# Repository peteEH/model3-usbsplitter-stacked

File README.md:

# model3-usbsplitter-stacked
stacked usb splitter for model 3, end launch

BOM to get the splitter assembled

Part Number     Quantity    Comments
5787745-2       1           double stacked, type-A, USB receptacle
UP2-AH-1-TH     1           plug, type-A, usb
4.7uF Cap       1           Any capacitor, 0805 package, 10V or higher rating, 1uF to 6.8uF cap range
2 ohm res       1           0805 package, 1.5 to 3 ohms
22uF Cap        1           Any capacitor, 1210 package, 10V or higher rating, 10uF to 47uF cap range

PCB             1           Order PCB from JLC PCB or similar fab house   (QTY 5 for $2 @ JLC)

## LICENSE ##
Hardware License is Creative Commons - Attribution 3.0

Feel free to use these files to learn, explore electronics.

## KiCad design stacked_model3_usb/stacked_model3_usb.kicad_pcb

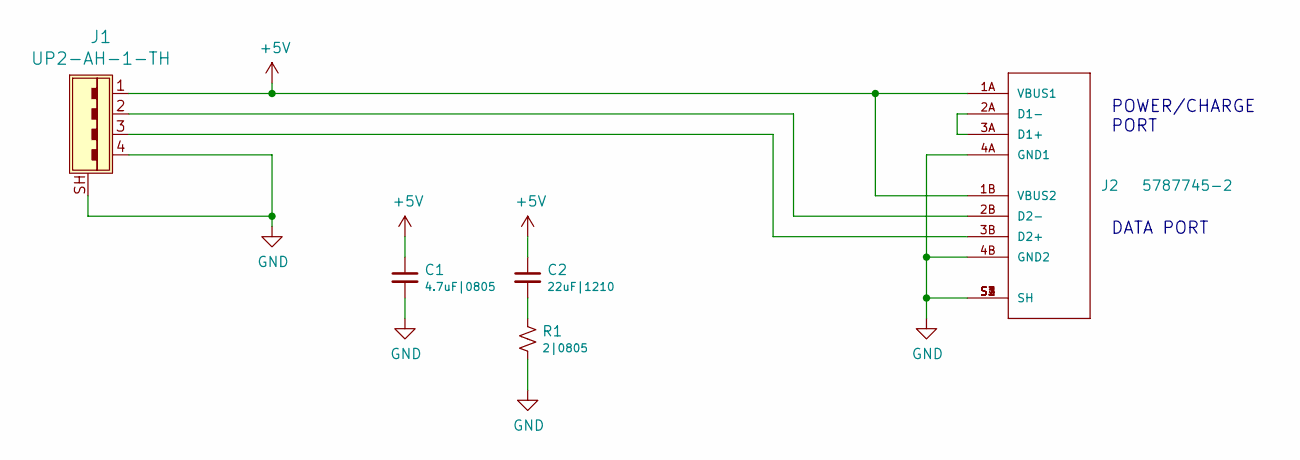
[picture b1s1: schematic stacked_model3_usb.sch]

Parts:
C1: 4.7uF|0805; C_0805_2012Metric
C2: 22uF|1210; C_1210_3225Metric
J1: UP2-AH-1-TH; USB_Male_A_UP2-AH-1-TH; MPN UP2-AH-1-TH; Digi-Key_PN 102-3996-ND
J2: 5787745-2; TE_5787745-2
R1: 2|0805; R_0805_2012Metric

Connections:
+5V: C1.1, C2.1, J1.1, J2.1A (VBUS1), J2.1B (VBUS2)
GND: C1.2, J1.4, J1.SH, J2.4A (GND1), J2.4B (GND2), J2.S1 (SH), J2.S2 (SH), J2.S3 (SH), J2.S4 (SH), R1.2
unnamed: C2.2, R1.1
unnamed: J1.2, J2.2B (D2-)
unnamed: J1.3, J2.3B (D2+)
unnamed: J2.2A (D1-), J2.3A (D1+)

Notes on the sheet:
DATA PORT
POWER/CHARGE PORT

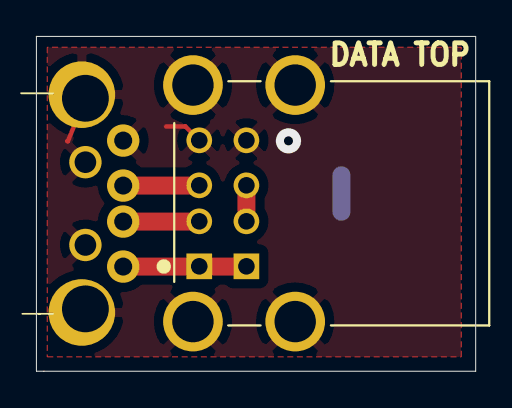
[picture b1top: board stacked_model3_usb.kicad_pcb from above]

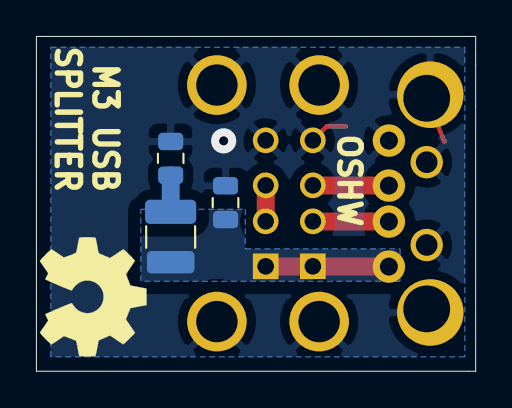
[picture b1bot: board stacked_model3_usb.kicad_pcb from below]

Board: 2 copper layers, 24.4 x 18.6 mm, 5 parts (3 on the bottom side), 6 nets.

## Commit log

2019-10-20 initial set of files uploaded
2019-10-20 updated readme, added BOM info
2019-10-26 added license
